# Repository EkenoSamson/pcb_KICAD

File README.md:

# pcb_KICAD
This repository contains my labs for KICAD.

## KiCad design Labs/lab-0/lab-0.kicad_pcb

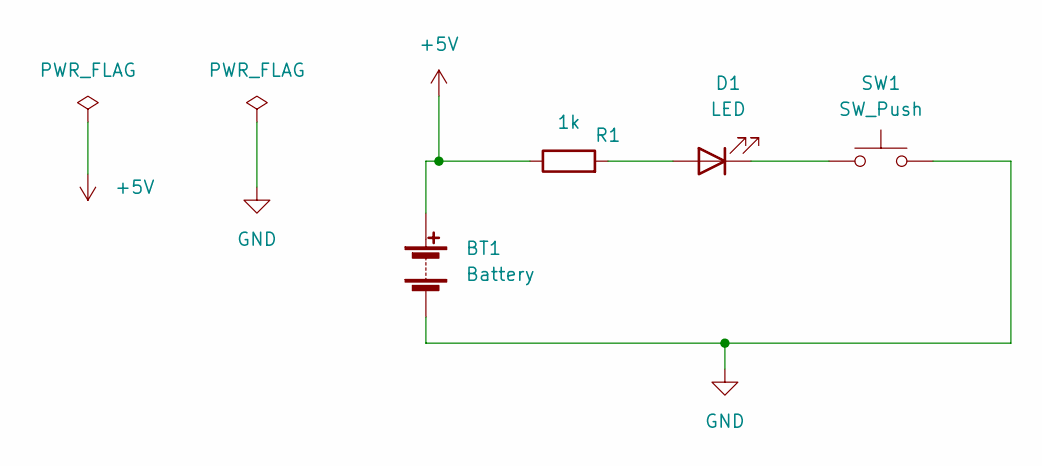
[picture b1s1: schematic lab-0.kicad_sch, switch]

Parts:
BT1: Battery; BatteryHolder_Keystone_107_1x23mm
D1: LED; LED_1206_3216Metric
R1: 1k; R_0612_1632Metric
SW1: SW_Push; Panasonic_EVQPUK_EVQPUB

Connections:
+5V: BT1.1 (+), R1.1
GND: BT1.2 (-), SW1.2
unnamed: D1.1 (K), SW1.1
unnamed: D1.2 (A), R1.2

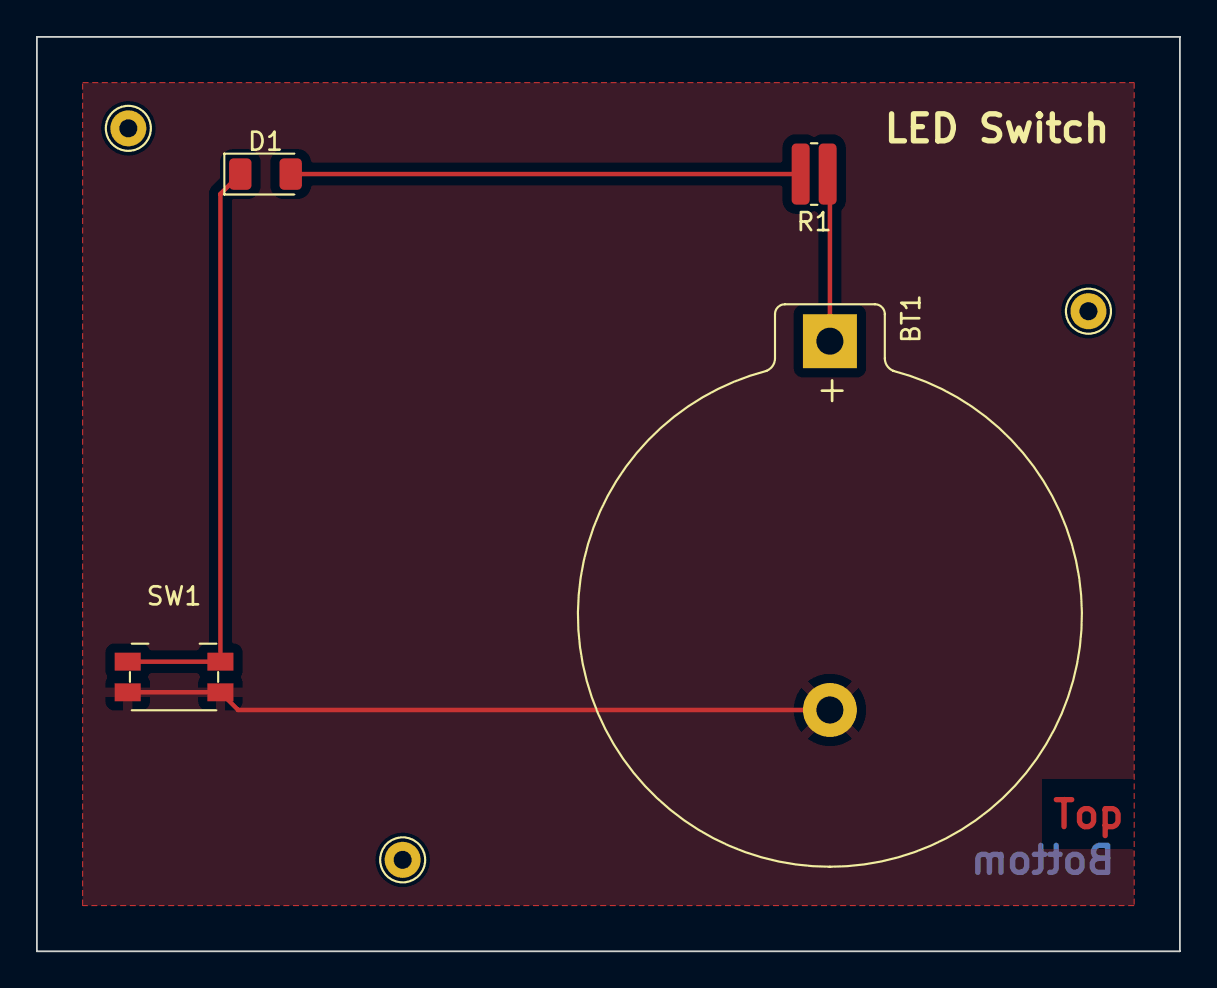
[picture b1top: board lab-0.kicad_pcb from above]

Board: 2 copper layers, 63.5 x 50.8 mm, 4 parts (0 on the bottom side), 4 nets.

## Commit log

2023-10-22 switch
2023-10-22 included descriptions
